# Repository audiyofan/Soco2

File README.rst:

=========================
SOCO2 PUSH PULL AMPLIFIER
=========================

Project authors:

- Pascal Benoist
- Grégoire Hubert
- Christophe Dedessus Les Moutier
- Yves Monmagnon

See http://audiyofan.org 

More information here http://www.audiyofan.org/forum/viewtopic.php?f=60&t=8371

Presentation
------------

Soco2 is a valve push-pull type amplifier delivering 10W in 8ohms with a low output impedance. It uses cheap Russian 6C19Π low impedance triodes as output valve and can be used without global feedback.

The built_version
------------------

The project was made on printed circuit board ( all files are included in Kicad folder )

This version does not use the PNK,

And the 6S19P's CCS is decoupled and has zener protection that prevents slippage cathode voltage on the higer swing

Power is succinct and yet respects the constants time

Local feedback of -1 dB, improve the damping factor

.. image:: built_version/schematics/Soco2_built_amp.png
.. image:: built_version/schematics/Soco2_built_psu.png

Warning
-------

This schematic implies the use of **lethal voltages**. Maximum precautions must be observed when working with this kind of high voltages. Authors are **not** responsible in any way for any problems, damages or injuries that would result in the making of the work and / or use of this schematic (see LICENCE file).

Results
-------

Realisations emitted very natural, detailed and transparent sound with nice deep bass using speakers as low as 90dB/W/m. Measures showed -74dB THD for 1/2W output and -65dB THD for 1W (H2 and H3) with matched tubes. Output can reach 13W with -40dB THD in 8Ω. 
    
.. image:: build/schematics/amplifier.png
.. image:: build/schematics/psu.png

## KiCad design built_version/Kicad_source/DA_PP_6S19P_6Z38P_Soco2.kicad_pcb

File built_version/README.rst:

=========================
SOCO2 PUSH PULL AMPLIFIER
=========================

Project authors:

- Pascal Benoist
- Grégoire Hubert
- Christophe Dedessus Les Moutier
- Yves Monmagnon

See http://audiyofan.org 

More information here http://www.audiyofan.org/forum/viewtopic.php?f=60&t=8371

The built_version
------------------

The project was made on printed circuit board ( all files are included in Kicad folder )

This version does not use the PNK,

And the 6S19P's CCS is decoupled and has zener protection that prevents slippage cathode voltage on the higer swing

Power is succinct and yet respects the constants time

Local feedback of -1 dB, improve the damping factor

Warning
-------

This schematic implies the use of **lethal voltages**. Maximum precautions must be observed when working with this kind of high voltages. Authors are **not** responsible in any way for any problems, damages or injuries that would result in the making of the work and / or use of this schematic (see LICENCE file).

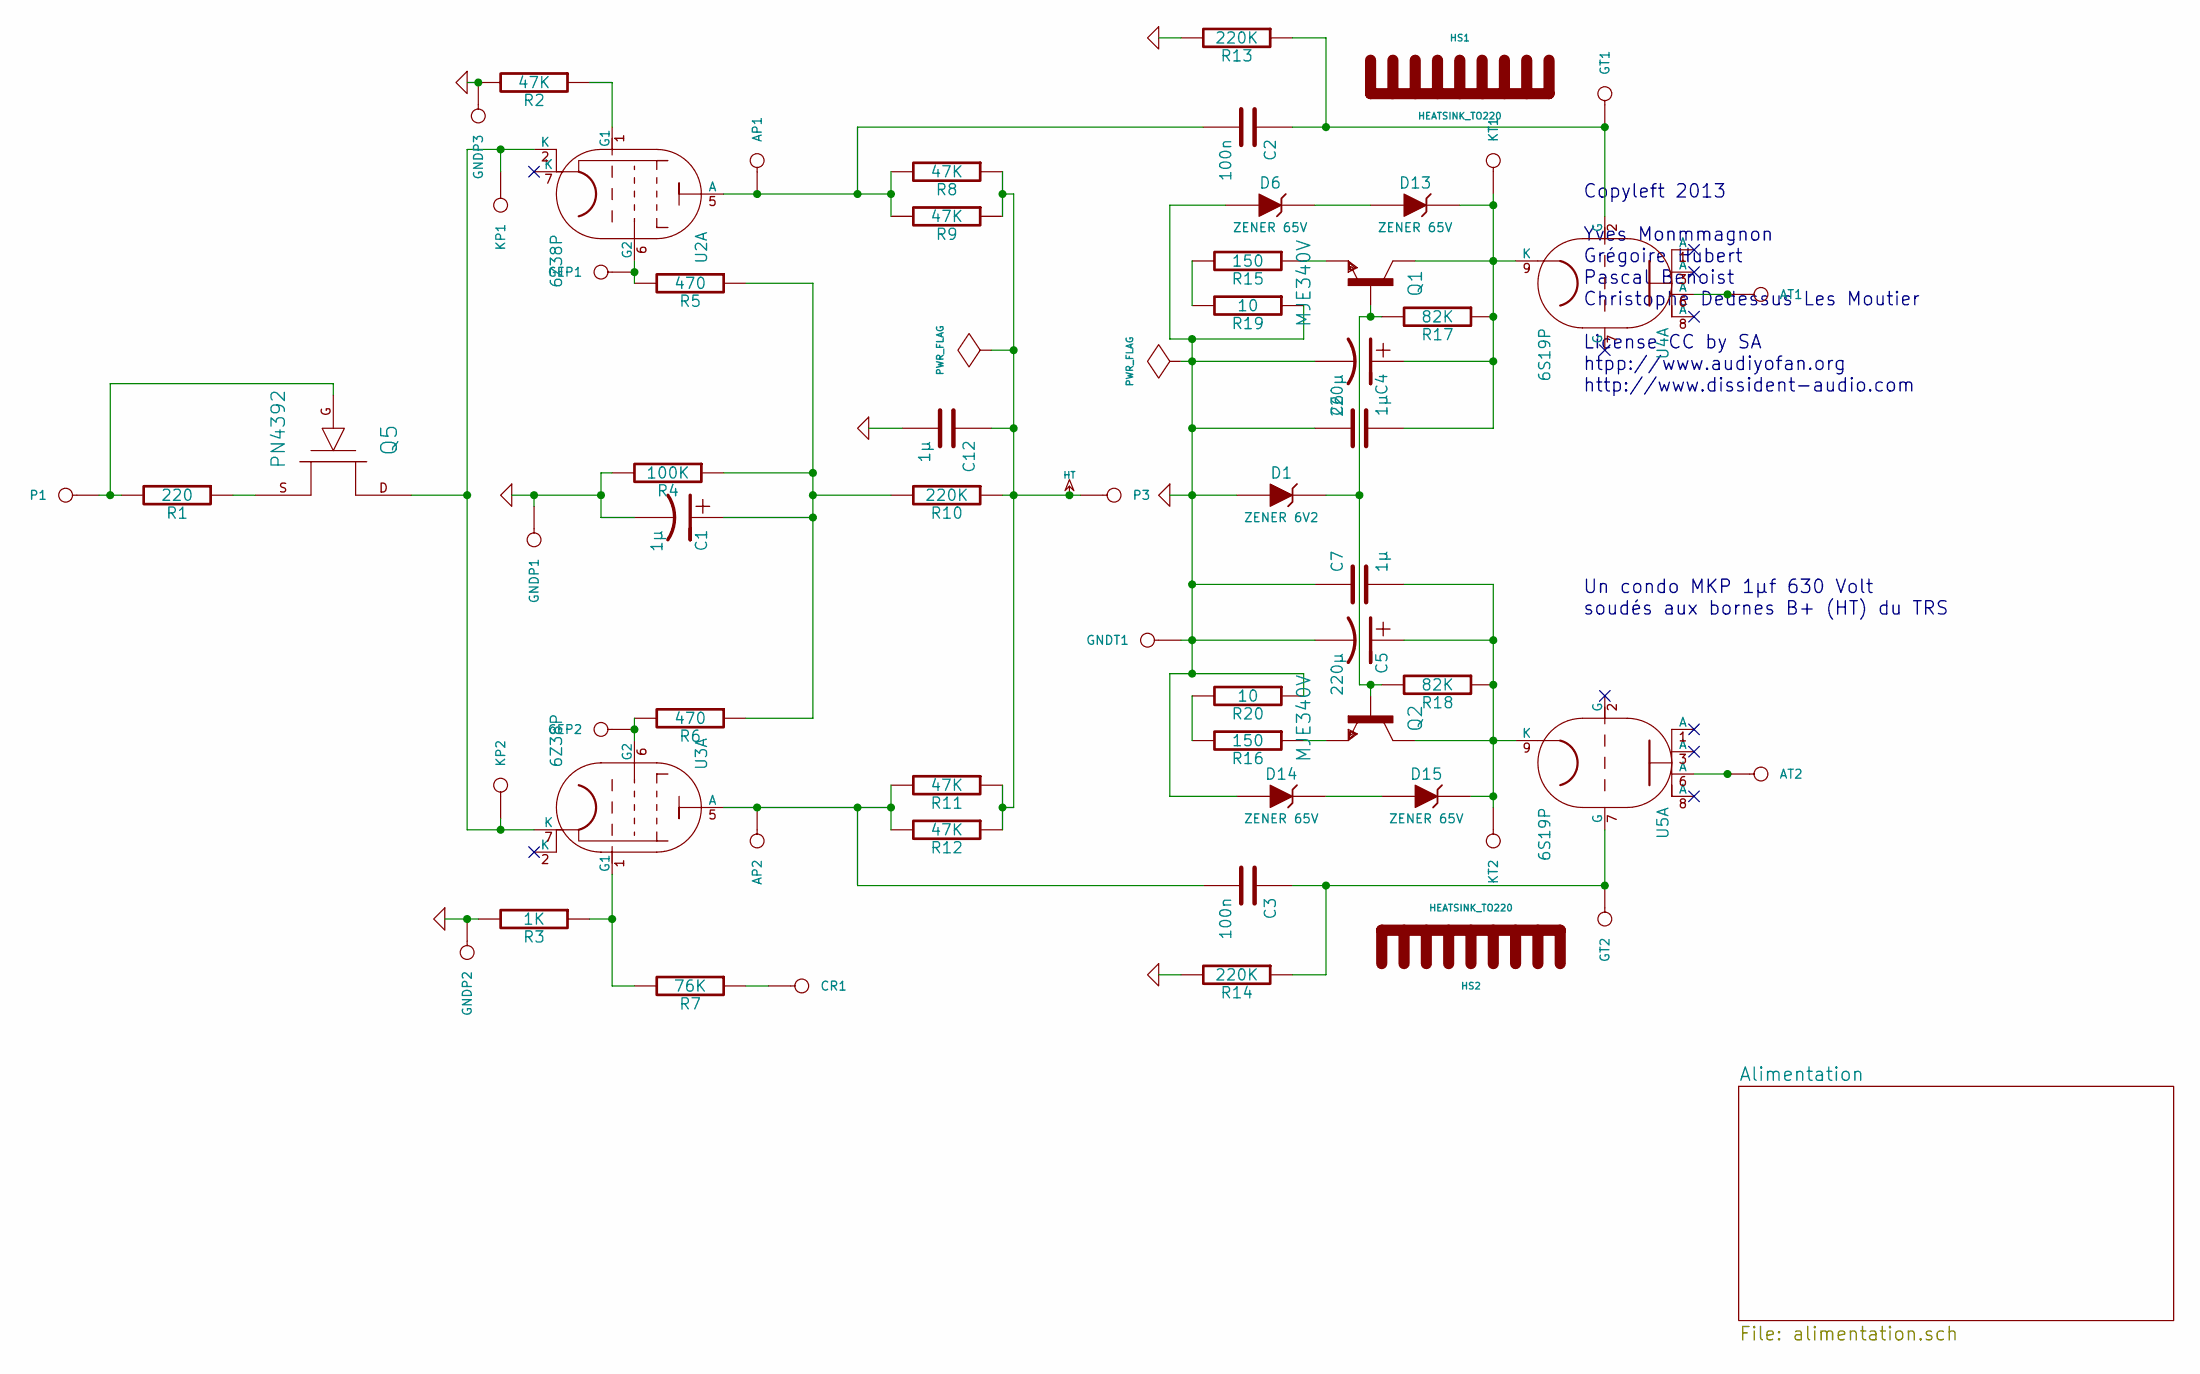
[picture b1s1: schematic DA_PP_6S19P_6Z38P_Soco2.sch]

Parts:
AP1: CONN_GNDE
AP2: CONN
AT1, AT2: CONN
C1, C6, C7, C12: 1µ
C2, C3: 100n
C4, C5: 220µ
CR1: CONN
D1: ZENER 6V2
D6, D13, D14, D15: ZENER 65V
GEP1, GEP2: CONN
GNDP1, GNDP2, GNDP3: CONN
GNDT1: CONN
GT1, GT2: CONN
HS1, HS2: HEATSINK_TO220
KP1, KP2: CONN
KT1, KT2: CONN
P1: CONN_VCC-
P3: CONN_HT
Q1, Q2: MJE340V
Q5: PN4392
R1: 220
R2, R8, R9, R11, R12: 47K
R3: 1K
R4: 100K
R5, R6: 470
R7: 76K
R10, R13, R14: 220K
R15, R16: 150
R17, R18: 82K
R19, R20: 10
U2, U3: 6Z38P; VALVE-NOVAL_P
U4, U5: 6S19P; VALVE-NOVAL_P

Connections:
GND: C1.2, C4.2, C5.2, C6.1, C7.1, C12.2, D1.1 (A), D6.1 (A), D14.1 (A), GNDP1.1, GNDP2.1, GNDP3.1, GNDT1.1, R2.2, R3.2, R4.2, R13.2, R14.2, R19.1, R20.1; also elsewhere on the board
HT: C12.1, P3.1, R8.1, R9.1, R10.1, R11.1, R12.1
unnamed: Q5.S, R1.1
unnamed: D1.2 (K), Q1.B, Q2.B, R17.2, R18.2
unnamed: C5.1, C7.2, D15.2 (K), KT2.1, Q2.C, R18.1, U5.9 (K)
unnamed: R15.2, R19.2
unnamed: Q1.E, R15.1
unnamed: R16.2, R20.2
unnamed: Q2.E, R16.1
unnamed: C3.1, GT2.1, R14.1, U5.7 (G)
unnamed: CR1.1, R7.1
unnamed: AP1.1, C2.2, R8.2, R9.2, U2.5 (A)
unnamed: GEP2.1, R6.2, U3.6 (G2)
unnamed: GEP1.1, R5.2, U2.6 (G2)
unnamed: AT1.1, U4.6 (A)
unnamed: D6.2 (K), D13.1 (A)
unnamed: AT2.1, U5.6 (A)
unnamed: D14.2 (K), D15.1 (A)
unnamed: R2.1, U2.1 (G1)
unnamed: R3.1, R7.2, U3.1 (G1)
unnamed: C4.1, C6.2, D13.2 (K), KT1.1, Q1.C, R17.1, U4.9 (K)
unnamed: C1.1, R4.1, R5.1, R6.1, R10.2
unnamed: KP1.1, KP2.1, Q5.D, U2.2 (K), U3.7 (K)
unnamed: P1.1, Q5.G, R1.2
unnamed: AP2.1, C3.2, R11.2, R12.2, U3.5 (A)
unnamed: C2.1, GT1.1, R13.1, U4.2 (G)

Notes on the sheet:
Un condo MKP 1µf 630 Volt soudés aux bornes B+ (HT) du TRS
Copyleft 2013 Yves Monmmagnon Grégoire Hubert Pascal Benoist Christophe Dedessus Les Moutier License CC by SA htpp://www.audiyofan.org http://www.dissident-audio.com

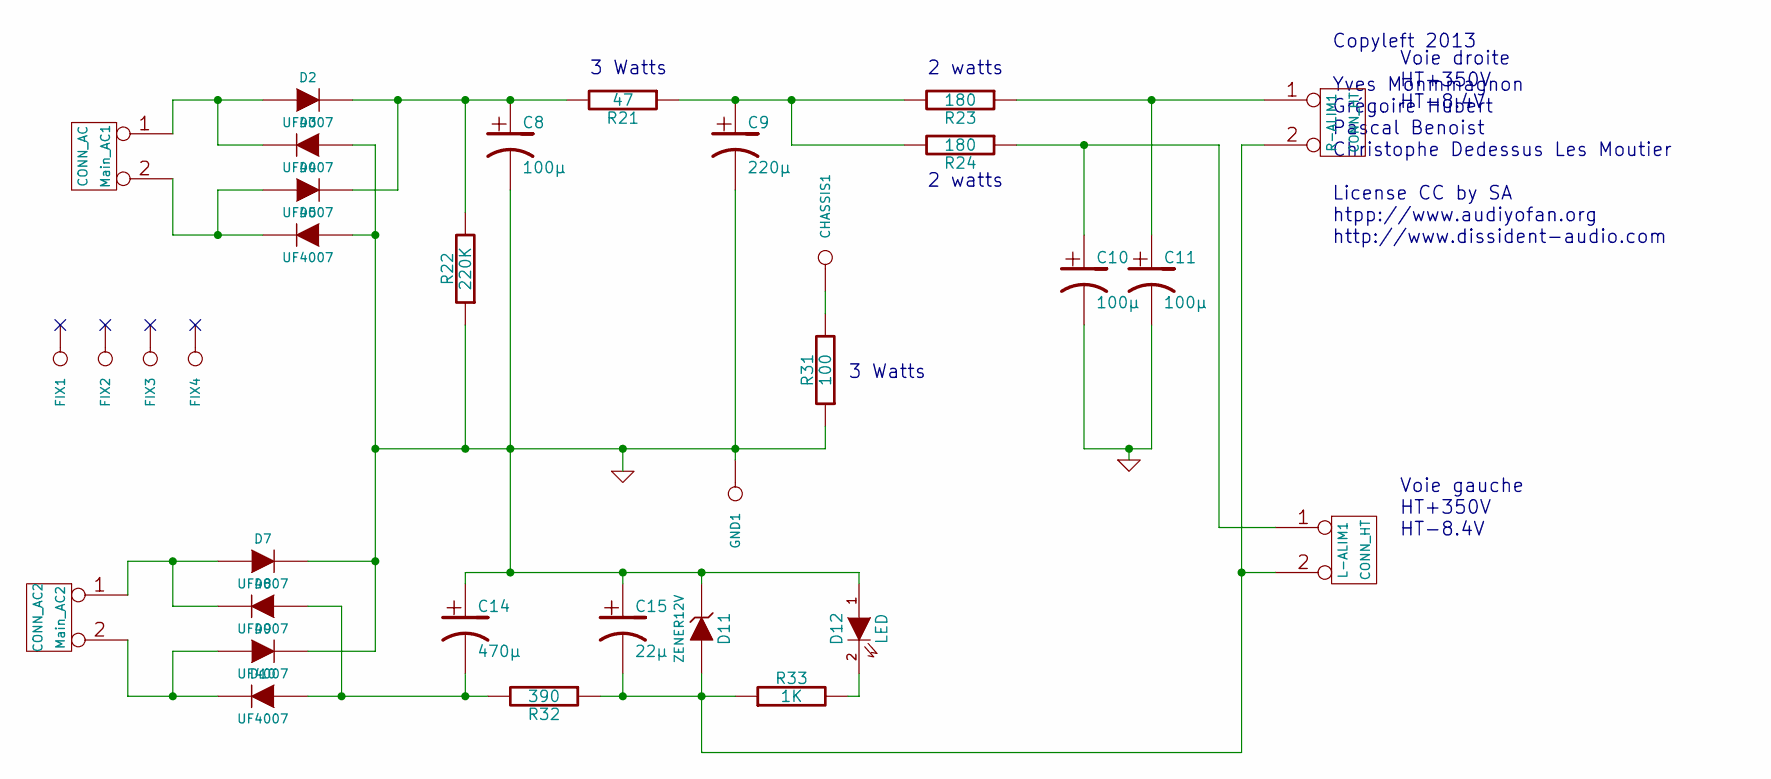
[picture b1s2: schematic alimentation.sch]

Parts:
C8, C10, C11: 100µ
C9: 220µ
C14: 470µ
C15: 22µ
CHASSIS1: CONN_CHASSIS
D2, D3, D4, D5, D7, D8, D9, D10: UF4007
D11: ZENER12V
D12: LED
FIX1, FIX2, FIX3, FIX4: FIX
GND1: CONN_GND
L-ALIM1: CONN_HT
Main_AC1: CONN_AC
Main_AC2: CONN_AC2
R21: 47
R22: 220K
R23, R24: 180
R31: 100
R32: 390
R33: 1K
R-ALIM1: CONN_HT

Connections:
GND: C8.2, C9.2, C10.2, C11.2, C14.1, C15.1, D3.1 (A), D5.1 (A), D7.2 (K), D9.2 (K), D11.2 (K), D12.1 (A), GND1.1, R22.1, R31.1; also elsewhere on the board
unnamed: D7.1 (A), D8.2 (K), Main_AC2.1
unnamed: C14.2, D8.1 (A), D10.1 (A), R32.2
unnamed: D12.2 (K), R33.2
unnamed: C9.1, R21.1, R23.2, R24.2
unnamed: C8.1, D2.2 (K), D4.2 (K), R21.2, R22.2
unnamed: CHASSIS1.1, R31.2
unnamed: D4.1 (A), D5.2 (K), Main_AC1.2 (PM)
unnamed: C10.1, L-ALIM1.1, R24.1
unnamed: D9.1 (A), D10.2 (K), Main_AC2.2 (PM)
unnamed: C15.2, D11.1 (A), L-ALIM1.2 (PM), R32.1, R33.1, R-ALIM1.2 (PM)
unnamed: D2.1 (A), D3.2 (K), Main_AC1.1
unnamed: C11.1, R23.1, R-ALIM1.1

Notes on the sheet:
Voie gauche HT+350V HT-8.4V
3 Watts
2 watts
Voie droite HT+350V HT-8.4V
Copyleft 2013 Yves Monmmagnon Grégoire Hubert Pascal Benoist Christophe Dedessus Les Moutier License CC by SA htpp://www.audiyofan.org http://www.dissident-audio.com

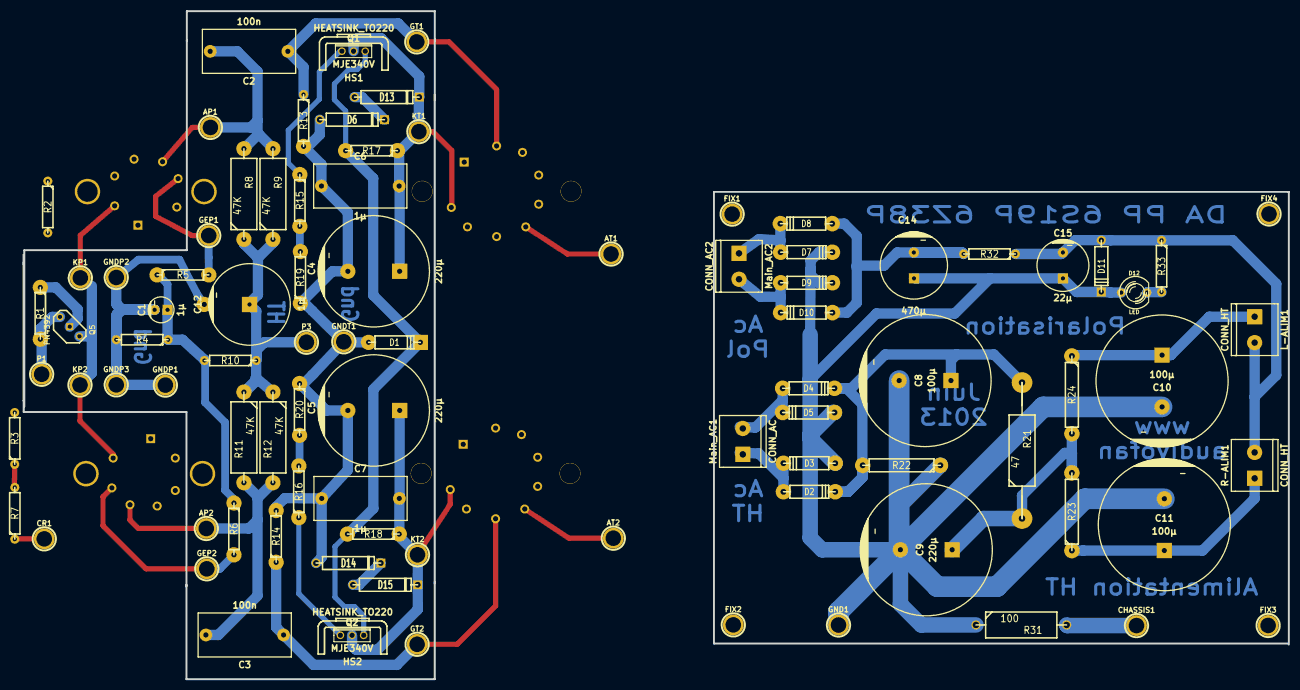
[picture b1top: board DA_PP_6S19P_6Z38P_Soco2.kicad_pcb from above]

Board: 2 copper layers, 248.2 x 131.0 mm, 94 parts (0 on the bottom side), 38 nets.

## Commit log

2012-10-19 Current project status.
2012-12-22 README and LICENCE.
2012-12-22 Renamed schemas to schematics.
2012-12-22 Changed the CCS in phase splitter.
2012-12-23 1µF CCS bypass MKP ported to 200V.
2013-02-17 -4dB feedback added.
2013-07-26 Adding built_version from Totof
2013-07-27 Adding a branch called totof
